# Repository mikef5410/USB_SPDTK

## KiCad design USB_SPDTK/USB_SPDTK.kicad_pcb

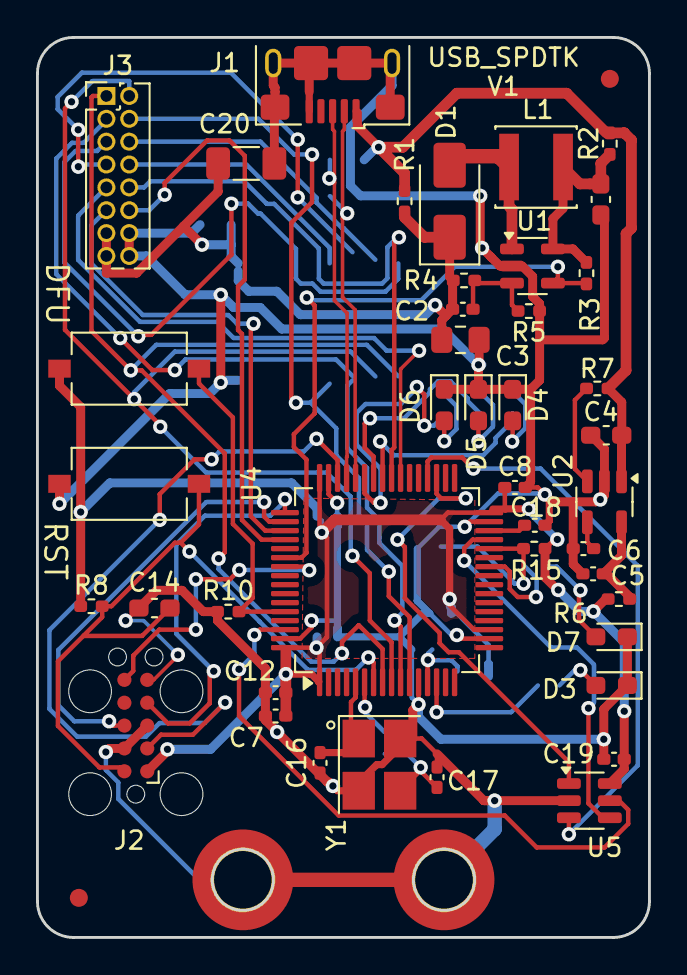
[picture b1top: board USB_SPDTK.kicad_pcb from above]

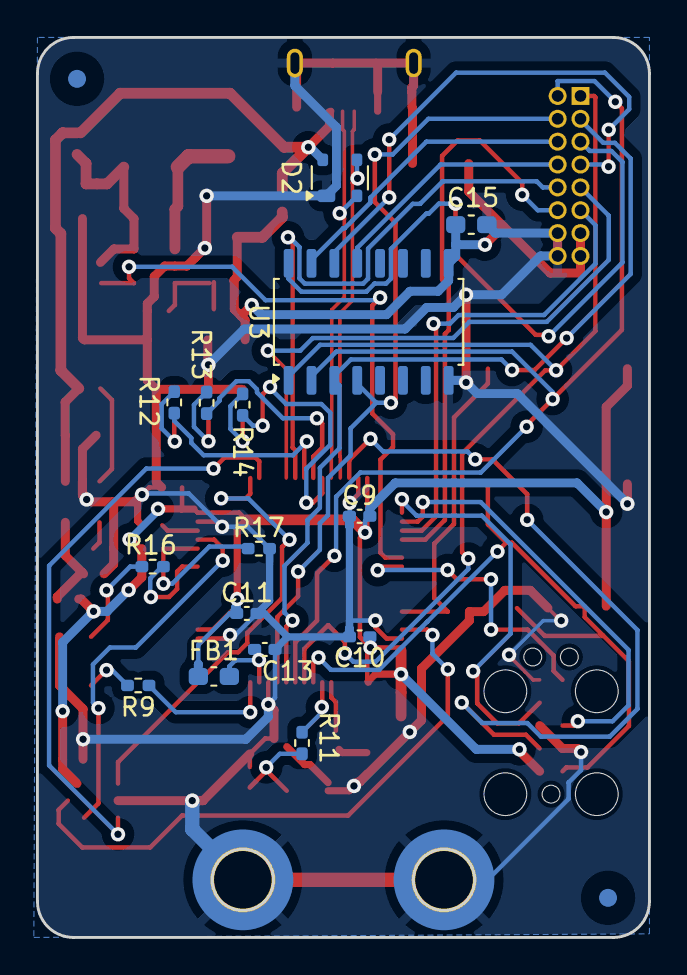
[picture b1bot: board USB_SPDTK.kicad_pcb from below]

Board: 2 copper layers, 34.0 x 50.0 mm, 63 parts (17 on the bottom side), 51 nets.

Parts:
C1, C4, C14, C15: 1u; C_0603_1608Metric_Pad1.08x0.95mm_HandSolder
C2: 220p; C_0402_1005Metric_Pad0.74x0.62mm_HandSolder
C3: 4.7u; C_0805_2012Metric_Pad1.18x1.45mm_HandSolder
C5, C7, C18: 4.7u; C_0402_1005Metric_Pad0.74x0.62mm_HandSolder
C6, C8, C9, C10, C11, C12, C13, C19: 0.1u; C_0402_1005Metric_Pad0.74x0.62mm_HandSolder
C16, C17: 30pF; C_0402_1005Metric_Pad0.74x0.62mm_HandSolder
C20: 22uF; C_1206_3216Metric_Pad1.33x1.80mm_HandSolder
D1: SS34; D_SMA
D2: PRTR5V0U2X; SOT-143
D3, D4, D5, D6: RED; LED_0603_1608Metric_Pad1.05x0.95mm_HandSolder
D7: GRN; LED_0603_1608Metric_Pad1.05x0.95mm_HandSolder
FB1: MMZ1608Y102B; C_0603_1608Metric_Pad1.08x0.95mm_HandSolder
FID1, FID2, FID3, FID4: Fiducial; Fiducial_1mm_Mask3mm
H1, H2: MountingHole_Pad; MountingHole_3.2mm_M3_DIN965_Pad_TopBottom
J1: USB_B_Micro; USB_Micro-B_Amphenol_10118193-0001LF_Horizontal
J2: TagConnectTC2050; Tag-Connect_TC2050-IDC-FP_2x05_P1.27mm_Vertical
J3: Conn_02x08_Odd_Even; PinHeader_2x08_P1.27mm_Vertical
L1: 10u; L_Changjiang_FNR4030S
R1, R2, R6: 0; R_0402_1005Metric_Pad0.72x0.64mm_HandSolder
R3, R7, R8, R10, R15: 10k; R_0402_1005Metric_Pad0.72x0.64mm_HandSolder
R4: 118k; R_0402_1005Metric_Pad0.72x0.64mm_HandSolder
R5: 13.3k; R_0402_1005Metric_Pad0.72x0.64mm_HandSolder
R9, R11, R12, R13, R14, R16, R17: 100; R_0402_1005Metric_Pad0.72x0.64mm_HandSolder
SW1, SW2: SW_Push; SW_Tactile_SPST_NO_Straight_CK_PTS636Sx25SMTRLFS
U1: LM27313XMF; SOT-23-5
U2: LP2985-3.3; SOT-23-5
U3: ULN2003ADR; SOIC-16_4.55x10.3mm_P1.27mm
U4: STM32F411RETx; LQFP-64_10x10mm_P0.5mm
U5: 93LC66AT-IOT; SOT-23-6
Y1: 16M 20pF 3225; Crystal_SMD_3225-4Pin_3.2x2.5mm_HandSoldering

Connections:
+3.3V: C7.1, C8.1, C9.2, C10.1, C11.1, C12.2, C19.2, FB1.1, J2.1 (VTref), R6.2, R8.1, R15.1, SW2.2, U4.1 (VBAT), U4.19 (VDD), U4.32 (VDD), U4.48 (VDD), U4.64 (VDD), U5.6 (Vcc)
+VSW: C2.1, C3.2, C15.2, C20.1, D1.1 (K), J3.13, J3.15, R1.2, R4.2, U3.9 (COM)
/Controller/BOOT1: R15.2, R17.1, U4.28 (PB2)
/Controller/JTCK: J2.4 (SWCLK/TCK), U4.49 (PA14)
/Controller/JTDI: J2.8 (NC/TDI), U4.50 (PA15)
/Controller/JTDO: J2.6 (SWO/TDO), U4.55 (PB3)
/Controller/JTMS: J2.2 (SWDIO/TMS), U4.46 (PA13)
/Controller/SPI2_MISO: U4.35 (PB14), U5.1 (DO)
/Controller/SPI2_MOSI: U4.36 (PB15), U5.3 (DI)
/Controller/SPI2_SCK: U4.29 (PB10), U5.4 (CLK)
/Controller/USB+: D2.3 (I/O2), J1.3 (D+), U4.45 (PA12)
/Controller/USB-: D2.2 (I/O1), J1.2 (D-), U4.44 (PA11)
/Controller/~SPI2NSS: U4.62 (PB9), U5.5 (CS)
Aux0: J3.9, U4.39 (PC8)
Aux1: J3.10, U4.40 (PC9)
Aux2: J3.11, U4.51 (PC10)
Aux3: J3.12, U4.52 (PC11)
GND: C1.1, C3.1, C4.1, C5.1, C6.1, C7.2, C8.2, C9.1, C10.2, C11.2, C12.1, C13.2, C14.1, C15.1, C16.2, C17.2, C18.1, C19.1, C20.2, D2.1 (GND), D3.1 (K), D4.1 (K), D5.1 (K), D6.1 (K), D7.1 (K), H1.1, H2.1, J1.5 (GND), J1.6 (Shield), J2.3 (GND), J2.5 (GND), J2.9 (GNDDetect), J3.14, J3.16, R5.1, R10.1, R17.2, SW1.2, U1.2 (GND), U2.2 (GND), U3.8 (GND), U4.12 (VSSA), U4.18 (VSS), U4.31 (VSS), U4.47 (VSS), U4.63 (VSS), U5.2 (Vss), Y1.2, Y1.4
HVEnable: R3.1, U1.4 (EN), U4.54 (PD2)
unnamed: C17.1, R11.1, Y1.3
unnamed: D1.2 (A), L1.2, U1.1 (SW)
unnamed: D3.2 (A), R9.2
unnamed: D4.2 (A), R12.2
unnamed: D5.2 (A), R13.2
unnamed: D6.2 (A), R14.2
unnamed: D7.2 (A), R16.2
unnamed: C14.2, J2.10 (~RESET), R8.2, SW1.1, U4.7 (NRST)
unnamed: C2.2, R4.1, R5.2, U1.3 (FB)
unnamed: C1.2, L1.1, R2.1, R3.2, U1.5 (VIN)
unnamed: C6.2, U2.4 (BP)
unnamed: R7.2, U2.3 (ON/~OFF)
unnamed: C5.2, R6.1, U2.5 (VOUT)
unnamed: R10.2, SW2.1, U4.60 (BOOT0)
unnamed: R9.1, U4.14 (PA0)
unnamed: R12.1, U4.41 (PA8)
unnamed: R13.1, U4.42 (PA9)
unnamed: R14.1, U4.43 (PA10)
unnamed: R16.1, U4.26 (PB0)
unnamed: C16.1, U4.5 (PH0), Y1.1
unnamed: R11.2, U4.6 (PH1)
unnamed: C18.2, U4.30 (VCAP1)
unnamed: C13.1, FB1.2, U4.13 (VDDA)
S1D: J3.2, U3.2 (I2), U4.9 (PC1)
S1D_OUT: J3.6, U3.15 (O2)
S1U: J3.1, U3.1 (I1), U4.8 (PC0)
S1U_OUT: J3.5, U3.16 (O1)
S2D: J3.4, U3.4 (I4), U4.11 (PC3)
S2D_OUT: J3.8, U3.13 (O4)
S2U: J3.3, U3.3 (I3), U4.10 (PC2)
S2U_OUT: J3.7, U3.14 (O3)
VBUS: C4.2, D2.4 (VCC), J1.1 (VBUS), R1.1, R2.2, R7.1, U2.1 (VIN)

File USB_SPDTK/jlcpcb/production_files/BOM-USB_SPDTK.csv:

Comment,Designator,Footprint,LCSC
C1,1u,C_0603_1608Metric_Pad1.08x0.95mm_HandSolder,C15849,,0,0
C10,0.1u,C_0402_1005Metric_Pad0.74x0.62mm_HandSolder,C5142567,,0,0
C11,0.1u,C_0402_1005Metric_Pad0.74x0.62mm_HandSolder,C5142567,,0,0
C12,0.1u,C_0402_1005Metric_Pad0.74x0.62mm_HandSolder,C5142567,,0,0
C13,0.1u,C_0402_1005Metric_Pad0.74x0.62mm_HandSolder,C5142567,,0,0
C14,1u,C_0603_1608Metric_Pad1.08x0.95mm_HandSolder,C15849,,0,0
C15,1u,C_0603_1608Metric_Pad1.08x0.95mm_HandSolder,C15849,,0,0
C16,30pF,C_0402_1005Metric_Pad0.74x0.62mm_HandSolder,C1658,,0,0
C17,30pF,C_0402_1005Metric_Pad0.74x0.62mm_HandSolder,C1658,,0,0
C18,4.7u,C_0402_1005Metric_Pad0.74x0.62mm_HandSolder,C106859,,0,0
C19,0.1u,C_0402_1005Metric_Pad0.74x0.62mm_HandSolder,C5142567,,0,0
C2,220p,C_0402_1005Metric_Pad0.74x0.62mm_HandSolder,C1603,,0,0
C20,22uF,C_1206_3216Metric_Pad1.33x1.80mm_HandSolder,C12891,,0,0
C3,4.7u,C_0805_2012Metric_Pad1.18x1.45mm_HandSolder,C1779,,0,0
C4,1u,C_0603_1608Metric_Pad1.08x0.95mm_HandSolder,C15849,,0,0
C5,4.7u,C_0402_1005Metric_Pad0.74x0.62mm_HandSolder,C106859,,0,0
C6,0.1u,C_0402_1005Metric_Pad0.74x0.62mm_HandSolder,C5142567,,0,0
C7,4.7u,C_0402_1005Metric_Pad0.74x0.62mm_HandSolder,C106859,,0,0
C8,0.1u,C_0402_1005Metric_Pad0.74x0.62mm_HandSolder,C5142567,,0,0
C9,0.1u,C_0402_1005Metric_Pad0.74x0.62mm_HandSolder,C5142567,,0,0
D1,SS34,D_SMA,C8678,,0,0
D2,PRTR5V0U2X,SOT-143,C2827688,,0,0
D3,RED,LED_0603_1608Metric_Pad1.05x0.95mm_HandSolder,C84263,,0,0
D4,RED,LED_0603_1608Metric_Pad1.05x0.95mm_HandSolder,C84263,,0,0
D5,RED,LED_0603_1608Metric_Pad1.05x0.95mm_HandSolder,C84263,,0,0
D6,RED,LED_0603_1608Metric_Pad1.05x0.95mm_HandSolder,C84263,,0,0
D7,GRN,LED_0603_1608Metric_Pad1.05x0.95mm_HandSolder,C434423,,0,0
FB1,MMZ1608Y102B,C_0603_1608Metric_Pad1.08x0.95mm_HandSolder,C114771,,0,0
J1,USB_B_Micro,USB_Micro-B_Amphenol_10118193-0001LF_Horizontal,C132562,,0,0
L1,10u,L_Changjiang_FNR4030S,C167879,,0,0
R10,10k,R_0402_1005Metric_Pad0.72x0.64mm_HandSolder,C25744,,0,0
R11,100,R_0402_1005Metric_Pad0.72x0.64mm_HandSolder,C25076,,0,0
R12,100,R_0402_1005Metric_Pad0.72x0.64mm_HandSolder,C25076,,0,0
R13,100,R_0402_1005Metric_Pad0.72x0.64mm_HandSolder,C25076,,0,0
R14,100,R_0402_1005Metric_Pad0.72x0.64mm_HandSolder,C25076,,0,0
R15,10k,R_0402_1005Metric_Pad0.72x0.64mm_HandSolder,C25744,,0,0
R16,100,R_0402_1005Metric_Pad0.72x0.64mm_HandSolder,C25076,,0,0
R17,100,R_0402_1005Metric_Pad0.72x0.64mm_HandSolder,C25076,,0,0
R2,0,R_0402_1005Metric_Pad0.72x0.64mm_HandSolder,C17168,,0,0
R4,118k,R_0402_1005Metric_Pad0.72x0.64mm_HandSolder,C25748,,0,0
R5,13.3k,R_0402_1005Metric_Pad0.72x0.64mm_HandSolder,C122547,,0,0
R6,0,R_0402_1005Metric_Pad0.72x0.64mm_HandSolder,C17168,,0,0
R7,10k,R_0402_1005Metric_Pad0.72x0.64mm_HandSolder,C25744,,0,0
R8,10k,R_0402_1005Metric_Pad0.72x0.64mm_HandSolder,C25744,,0,0
R9,100,R_0402_1005Metric_Pad0.72x0.64mm_HandSolder,C25076,,0,0
SW1,SW_Push,SW_Tactile_SPST_NO_Straight_CK_PTS636Sx25SMTRLFS,C118141,,0,0
SW2,SW_Push,SW_Tactile_SPST_NO_Straight_CK_PTS636Sx25SMTRLFS,C118141,,0,0
U1,LM27313XMF,SOT-23-5,C341750,,0,0
U2,LP2985-3.3,SOT-23-5,C129375,,0,0
U3,ULN2003ADR,SOIC-16_4.55x10.3mm_P1.27mm,C7512,,0,0
U4,STM32F411RETx,LQFP-64_10x10mm_P0.5mm,C94355,,0,0
U5,93LC66AT-IOT,SOT-23-6,C511344,,0,0
Y1,16M 20pF 3225,Crystal_SMD_3225-4Pin_3.2x2.5mm_HandSoldering,C524727,,0,0

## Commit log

2024-06-07 Initial
2024-06-15 Update LCSC for pushbuttons
2024-06-17 JLC mfg artifacts re-gen'd
2024-06-19 Final submission to JLCPCB
2024-07-18 Add DowKey 401Y datasheet
2024-07-23 Add DowKey 401Y wiring guide
